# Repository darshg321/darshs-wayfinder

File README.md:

# darsh's wayfinder

a rhythm game with 4 cherry MX switches, 4 leds, and 4 active buzzers - controlled by the XIAO RP2040

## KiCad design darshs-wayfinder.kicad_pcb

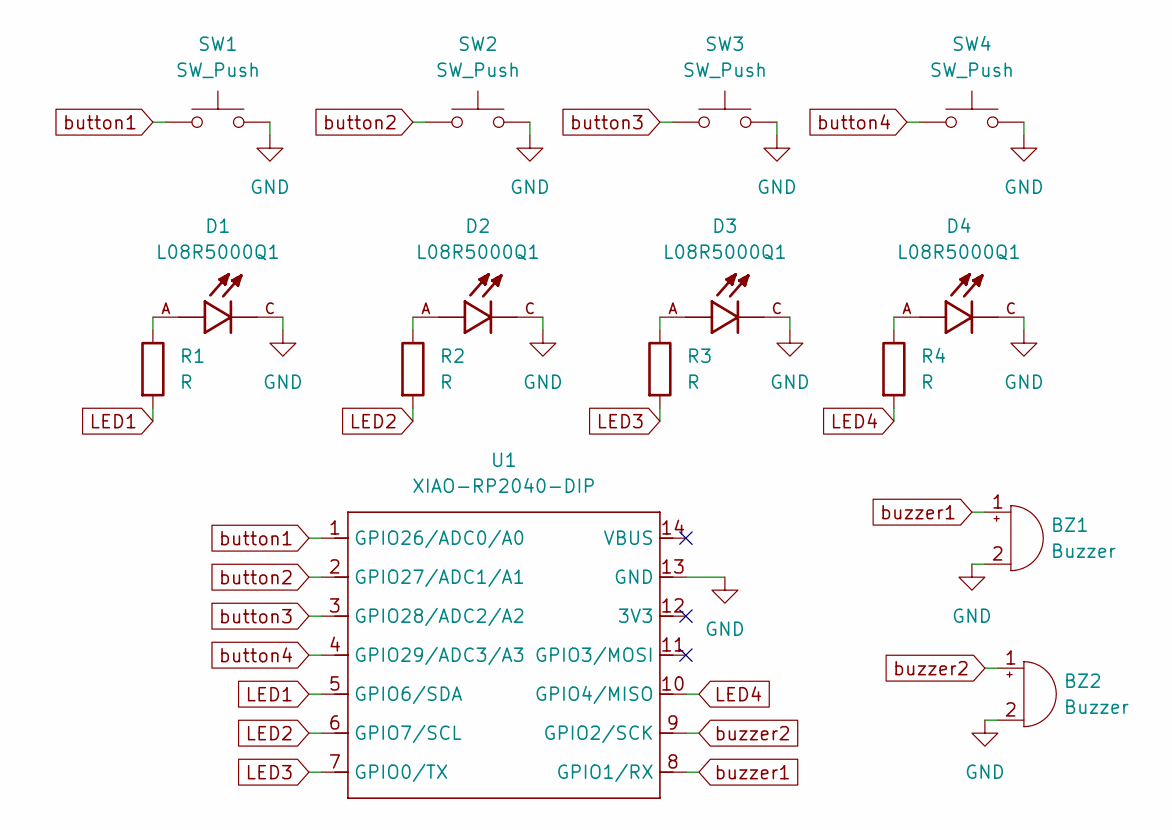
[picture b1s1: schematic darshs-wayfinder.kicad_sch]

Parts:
BZ1, BZ2: Buzzer; Buzzer_12x9.5RM7.6
D1, D2, D3, D4: L08R5000Q1; LEDRD254W57D500H1070; PARTREV NA
R1, R2, R3, R4: R; R_Axial_DIN0204_L3.6mm_D1.6mm_P5.08mm_Horizontal
SW1, SW2, SW3, SW4: SW_Push; SW_Cherry_MX_1.00u_PCB
U1: XIAO-RP2040-DIP

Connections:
GND: BZ1.2 (-), BZ2.2 (-), D1.C, D2.C, D3.C, D4.C, SW1.2, SW2.2, SW3.2, SW4.2, U1.13 (GND)
LED1: R1.2, U1.5 (GPIO6/SDA)
LED2: R2.2, U1.6 (GPIO7/SCL)
LED3: R3.2, U1.7 (GPIO0/TX)
LED4: R4.2, U1.10 (GPIO4/MISO)
unnamed: D1.A, R1.1
unnamed: D2.A, R2.1
unnamed: D3.A, R3.1
unnamed: D4.A, R4.1
button1: SW1.1, U1.1 (GPIO26/ADC0/A0)
button2: SW2.1, U1.2 (GPIO27/ADC1/A1)
button3: SW3.1, U1.3 (GPIO28/ADC2/A2)
button4: SW4.1, U1.4 (GPIO29/ADC3/A3)
buzzer1: BZ1.1 (+), U1.8 (GPIO1/RX)
buzzer2: BZ2.1 (+), U1.9 (GPIO2/SCK)

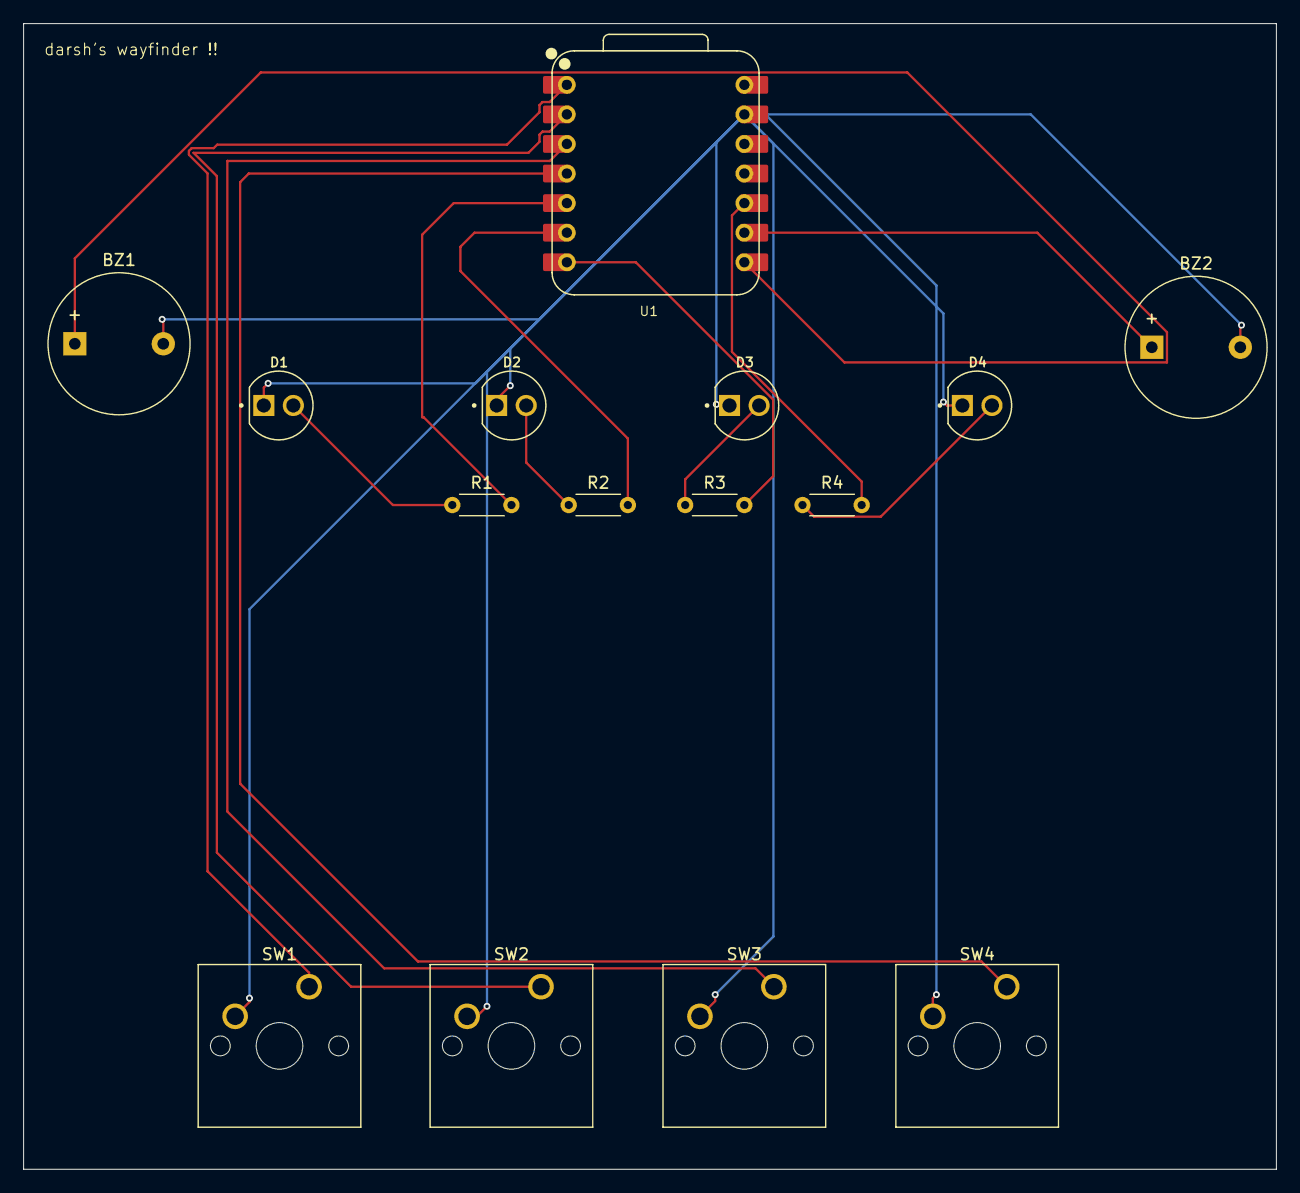
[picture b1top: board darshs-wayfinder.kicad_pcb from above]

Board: 2 copper layers, 107.6 x 98.4 mm, 15 parts (0 on the bottom side), 15 nets.

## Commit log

2025-07-27 wayfinder
